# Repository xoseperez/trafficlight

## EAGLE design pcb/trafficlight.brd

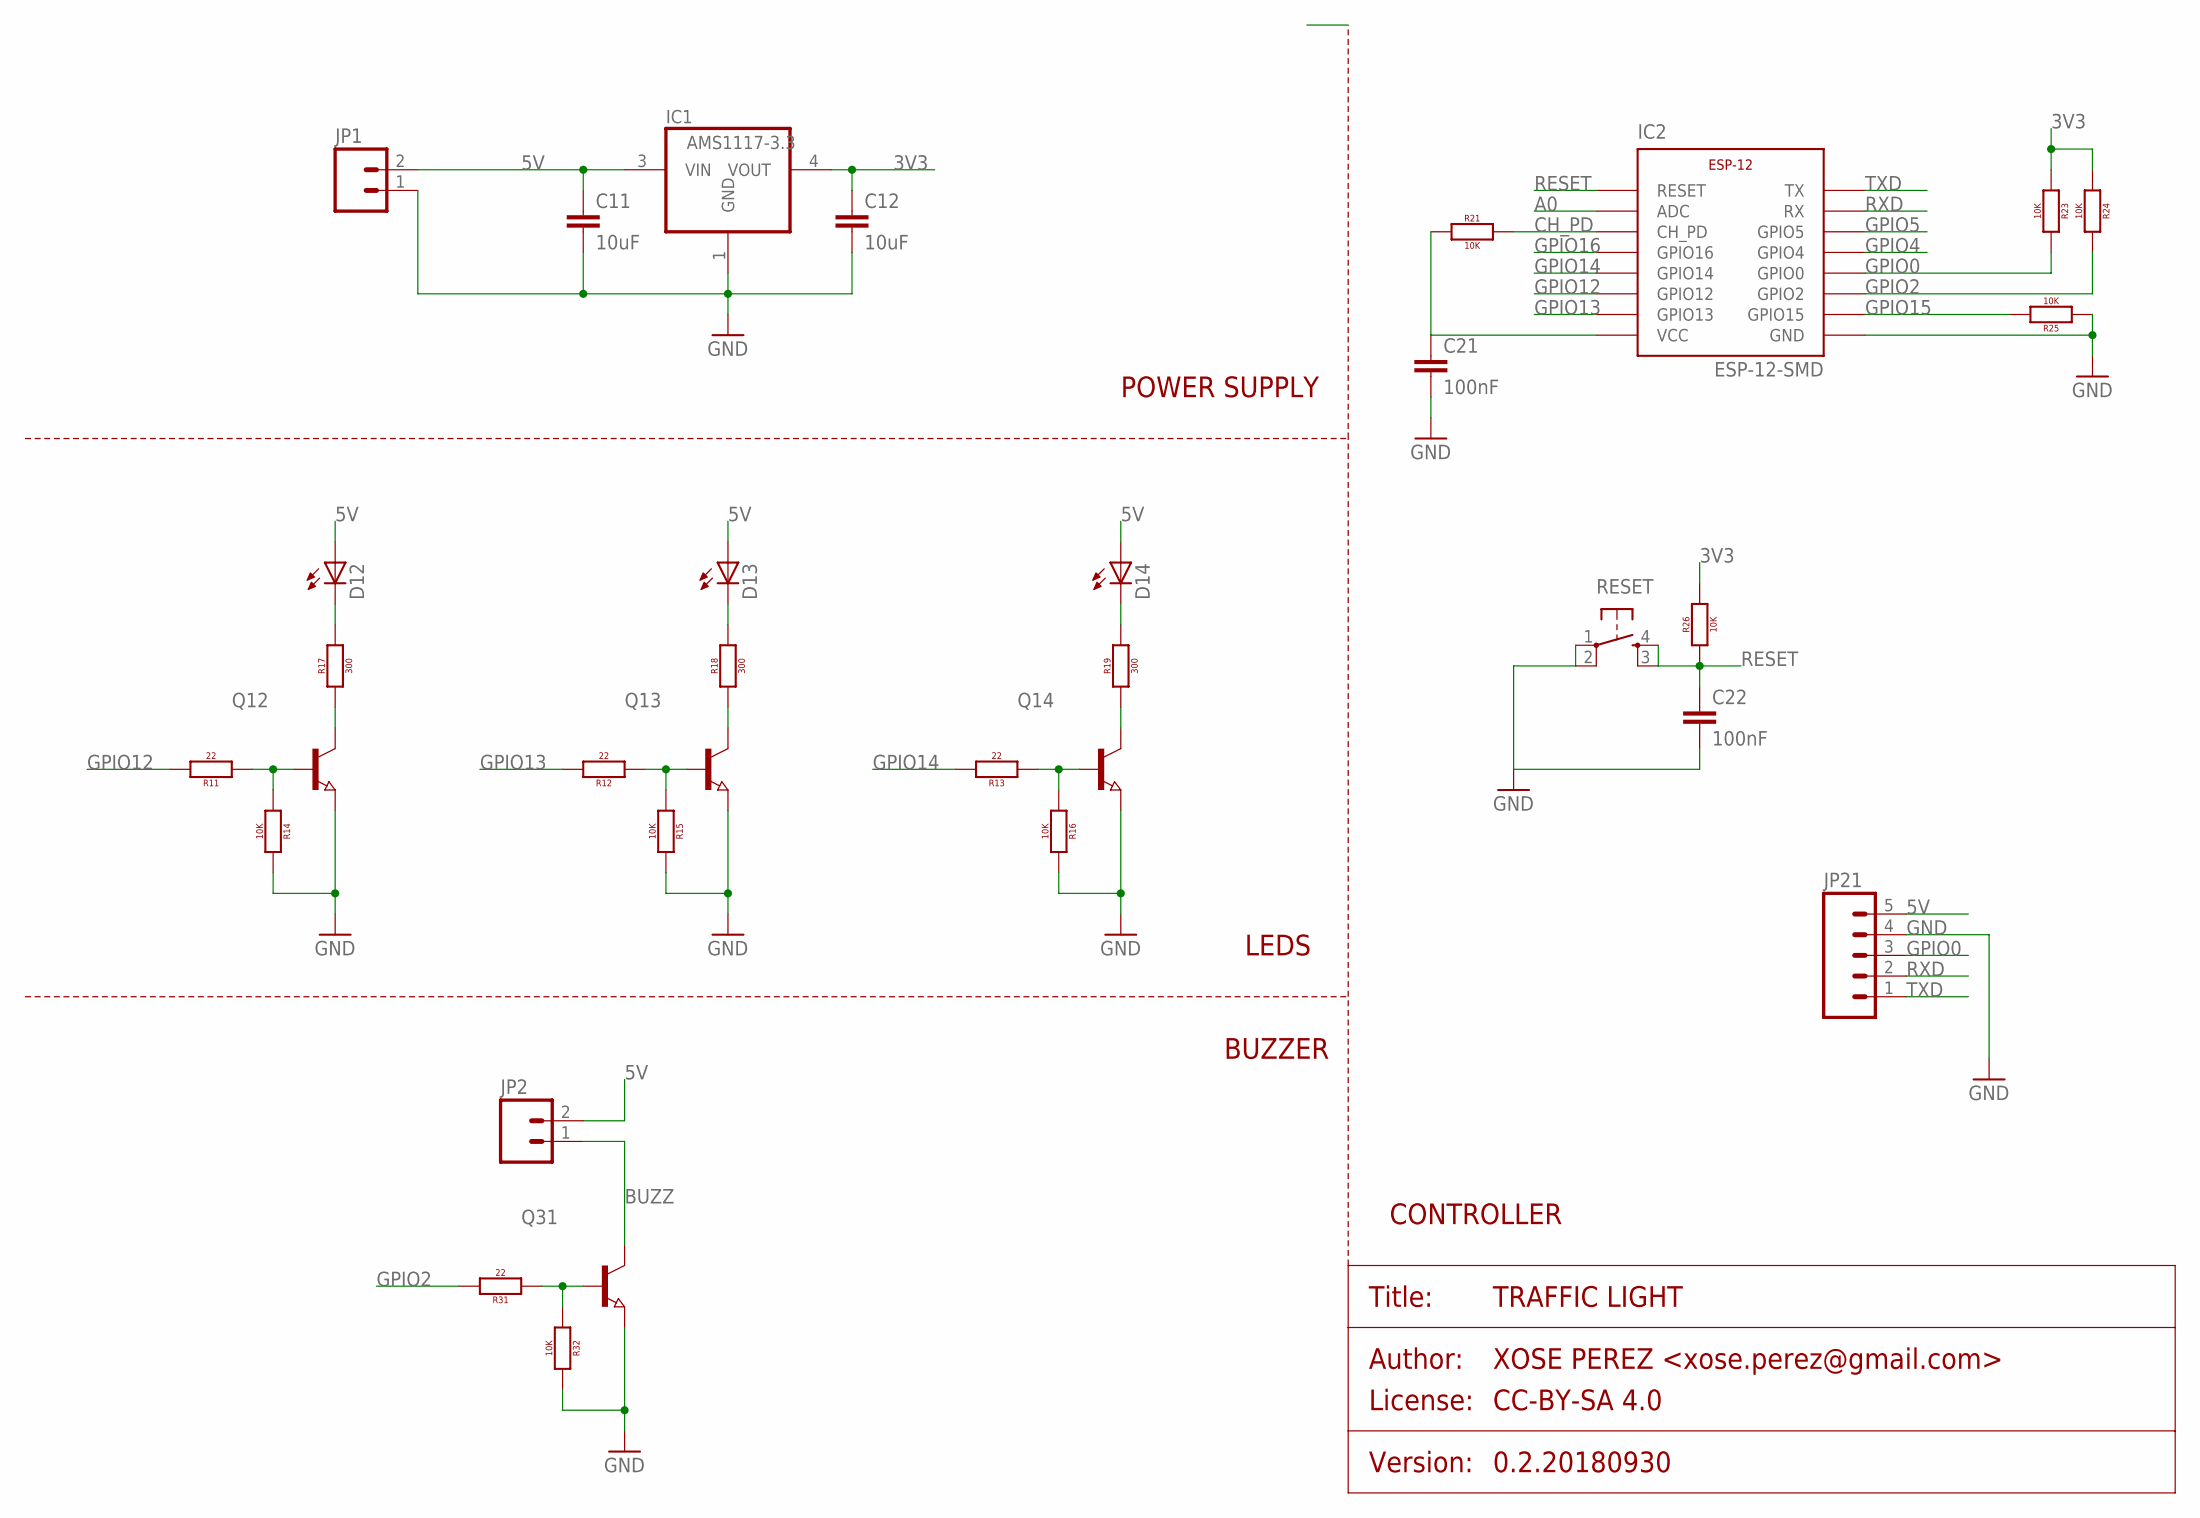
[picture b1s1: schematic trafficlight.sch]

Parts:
C11, C12: 10uF; 0805
C21, C22: 100nF; 0805
D12, D13, D14: LED5MM
IC1: AMS1117-3.3; SOT223
IC2: ESP-12-SMD
JP1, JP2: M02PTH; 1X02
JP21: M05PTH; 1X05
Q12, Q13, Q14, Q31: NPN-TRANSISTOR_SOT23; SOT23
R11, R12, R13, R31: 22; 0805
R14, R15, R16, R21, R23, R24, R25, R26, R32: 10K; 0805
R17, R18, R19: 300; 0805
RESET: TACTILE_BUTTON_SMD; TACTILE-BUTTON-SMD

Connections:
3V3: C12.1, C21.1, IC1.4 (VOUT), IC2.VCC, R21.1, R23.1, R24.1, R26.2
5V: C11.1, D12.A, D13.A, D14.A, IC1.3 (VIN), JP1.2, JP2.2, JP21.5
A0: IC2.ADC
BUZZ: JP2.1, Q31.3 (C)
CH_PD: IC2.CH_PD, R21.2
GND: C11.2, C12.2, C21.2, C22.2, IC1.1 (GND), IC2.GND, JP1.1, JP21.4, Q12.2 (E), Q13.2 (E), Q14.2 (E), Q31.2 (E), R14.2, R15.2, R16.2, R25.1, R32.2, RESET.1 (SWA1), RESET.2 (SWB1)
GPIO0: IC2.GPIO0, JP21.3, R23.2
GPIO2: IC2.GPIO2, R24.2, R31.2
GPIO4: IC2.GPIO4
GPIO5: IC2.GPIO5
GPIO12: IC2.GPIO12, R11.2
GPIO13: IC2.GPIO13, R12.2
GPIO14: IC2.GPIO14, R13.2
GPIO15: IC2.GPIO15, R25.2
GPIO16: IC2.GPIO16
unnamed: Q13.1 (B), R12.1, R15.1
unnamed: D13.K (C), R18.2
unnamed: Q12.1 (B), R11.1, R14.1
unnamed: Q13.3 (C), R18.1
unnamed: Q14.1 (B), R13.1, R16.1
unnamed: D14.K (C), R19.2
unnamed: Q14.3 (C), R19.1
unnamed: D12.K (C), R17.2
unnamed: Q12.3 (C), R17.1
unnamed: Q31.1 (B), R31.1, R32.1
RESET: C22.1, IC2.RESET, R26.1, RESET.3 (SWB2), RESET.4 (SWA2)
RXD: IC2.RX, JP21.2
TXD: IC2.TX, JP21.1

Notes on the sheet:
POWER SUPPLY
CONTROLLER
LEDS
BUZZER

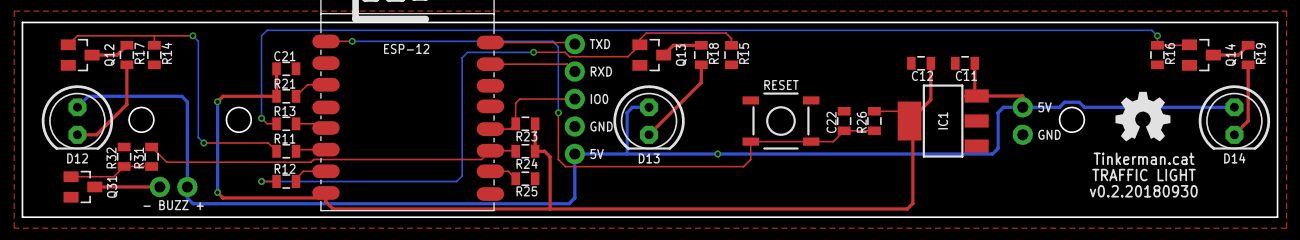
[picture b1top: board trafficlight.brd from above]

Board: 2 copper layers, 116.0 x 18.0 mm, 33 parts (0 on the bottom side), 24 nets.

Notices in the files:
pcb/trafficlight.sch:
PROJECT_LICENSE: CC-BY-SA 4.0
parts and their libraries:
SparkFun-Aesthetics: Licensing: Creative Commons ShareAlike 4.0 International - https://creativecommons.org/licenses/by-sa/4.0
